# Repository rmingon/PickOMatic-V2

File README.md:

# PickOMatic V2

> **Place faster. Place smarter. The open-source motion controller that turns your pick-and-place ambitions into production reality.**

<p align="center">

</p>

---

**PickOMatic V2** is a professional-grade, all-in-one motion control board designed from the ground up for desktop pick-and-place machines. It is the second generation of the [PickOMatic](https://github.com/rmingon/PickOMatic) motion controller, rebuilt around a modern 32-bit **RISC-V** microcontroller with native **Ethernet** and **USB-C** connectivity.

One board drives the entire machine: gantry, picker heads, nozzles, vacuum, lighting and feedback, with no shields, no breakout spaghetti and no compromises.

## Highlights

- **RISC-V power** : WCH **CH32V317VCT6** (QingKe 32-bit RISC-V core, LQFP-100), a massive leap over the 8-bit ATmega2560 of V1
- **7 stepper channels** : on-board **DRV8825** drivers for the XY gantry, Z axis and auxiliary picker-head axes, each with per-channel microstepping selection (M0/M1/M2 solder jumpers) and current trim
- **Ethernet on board** : integrated PHY with RJ45 magjack (HR911105A) for fast, reliable G-code streaming over the network
- **USB-C** : modern connectivity for setup, control and firmware workflows
- **Vacuum and pneumatics** : dedicated relay outputs (NC-COM-NO) for the vacuum pump and pneumatic accessories
- **3 servo outputs** : independent nozzle height / rotation control per picker head
- **5 endstop inputs** : dedicated limit-switch inputs for X, Y and Z homing (dual X and dual Y supported)
- **Inspection lighting** : dedicated LED control output for camera lighting
- **Operator feedback** : on-board buzzer and status LEDs
- **Expansion ready** : I²C bus, custom headers, FTDI UART header, SWD debug port and BOOT jumpers
- **Clean power architecture** : single 12 V input with on-board buck converters (TPS562200) and LDO rails for logic

## What's new in V2

| | PickOMatic V1 | **PickOMatic V2** |
|---|---|---|
| Microcontroller | ATmega2560 @ 16 MHz (8-bit AVR) | **CH32V317VCT6 (32-bit RISC-V)** |
| Host link | USB-UART (CH340C) | **Native USB-C + Ethernet (RJ45)** |
| Stepper channels | 8 | 7 x DRV8825 with per-axis microstep jumpers |
| Debug / programming | AVR-ISP | **SWD + FTDI UART + BOOT jumpers** |
| Networking | None | **On-board Ethernet PHY + magjack** |

## Board overview

| PCB layout | Schematic |
|:---:|:---:|
|  |  |

## Specifications

| Subsystem | Detail |
|---|---|
| MCU | WCH CH32V317VCT6, 32-bit RISC-V, LQFP-100, external crystal |
| Motion | 7 x DRV8825 stepper drivers (STEP/DIR), microstepping via M0/M1/M2 solder jumpers, current trim potentiometers |
| Axes | Dual-Y and dual-X gantry support, Z axis, auxiliary picker-head channels |
| Endstops | 5 inputs (Z, X-X, Y-Y) on a dedicated header |
| Servos | 3 PWM outputs for nozzle actuation |
| Pneumatics | Relay outputs with NC-COM-NO terminals for vacuum pump control |
| Lighting | Dedicated LED_CTL output for inspection lighting |
| Connectivity | USB-C, 10M Ethernet (RJ45 HR911105A), I²C expansion, FTDI UART |
| Debug | SWD (SWCLK/SWDIO), BOOT0/BOOT1 jumpers, reset button |
| Feedback | Buzzer, status LEDs |
| Power input | 12 V DC via screw terminal |
| Power rails | 12 V motor rail, 5 V and 3.3 V logic rails (TPS562200 buck converters + LDOs) |
| Form factor | 4-corner mounting holes, screw-terminal I/O on board edges |

## Repository structure

```
PickOMatic-V2/
├── hardware/               # KiCad project (schematic + PCB)
│   ├── hardware.kicad_pro
│   ├── hardware.kicad_sch
│   └── hardware.kicad_pcb
├── 3d.png                  # 3D render of the assembled board
├── pcb.png                 # PCB layout view
├── schematic.png           # Full schematic
├── LICENSE                 # CERN-OHL-S v2
└── README.md
```

## Getting started

1. **Clone** the repository
   ```bash
   git clone https://github.com/rmingon/PickOMatic-V2.git
   ```
2. **Open** `hardware/hardware.kicad_pro` in [KiCad](https://www.kicad.org/) (version 8 or later recommended)
3. **Review** the schematic and PCB, then export Gerbers and the BOM for your fab house
4. **Assemble**, set the DRV8825 current limits, configure microstepping with the solder jumpers, and connect your motors, endstops, servos and vacuum pump
5. **Flash** your firmware via SWD or the FTDI/BOOT bootloader path, and start placing parts

## Related projects

- [PickOMatic (V1)](https://github.com/rmingon/PickOMatic) : the original ATmega2560-based motion controller this board evolved from

## Contributing

Issues and pull requests are welcome. If you build a machine around PickOMatic V2, share it: photos, firmware ports and feeder designs all help the project grow.

## License

This project is open-source hardware, released under the **CERN Open Hardware Licence Version 2, Strongly Reciprocal (CERN-OHL-S-2.0)**.

You may use, study, modify, manufacture and distribute this design, provided that any modified versions are released under the same licence and that source is made available. See [LICENSE](LICENSE) for the full text.

Copyright © 2026 [rmingon](https://github.com/rmingon)

---

<p align="center"><i>PickOMatic V2, because your components deserve to be placed with confidence.</i></p>

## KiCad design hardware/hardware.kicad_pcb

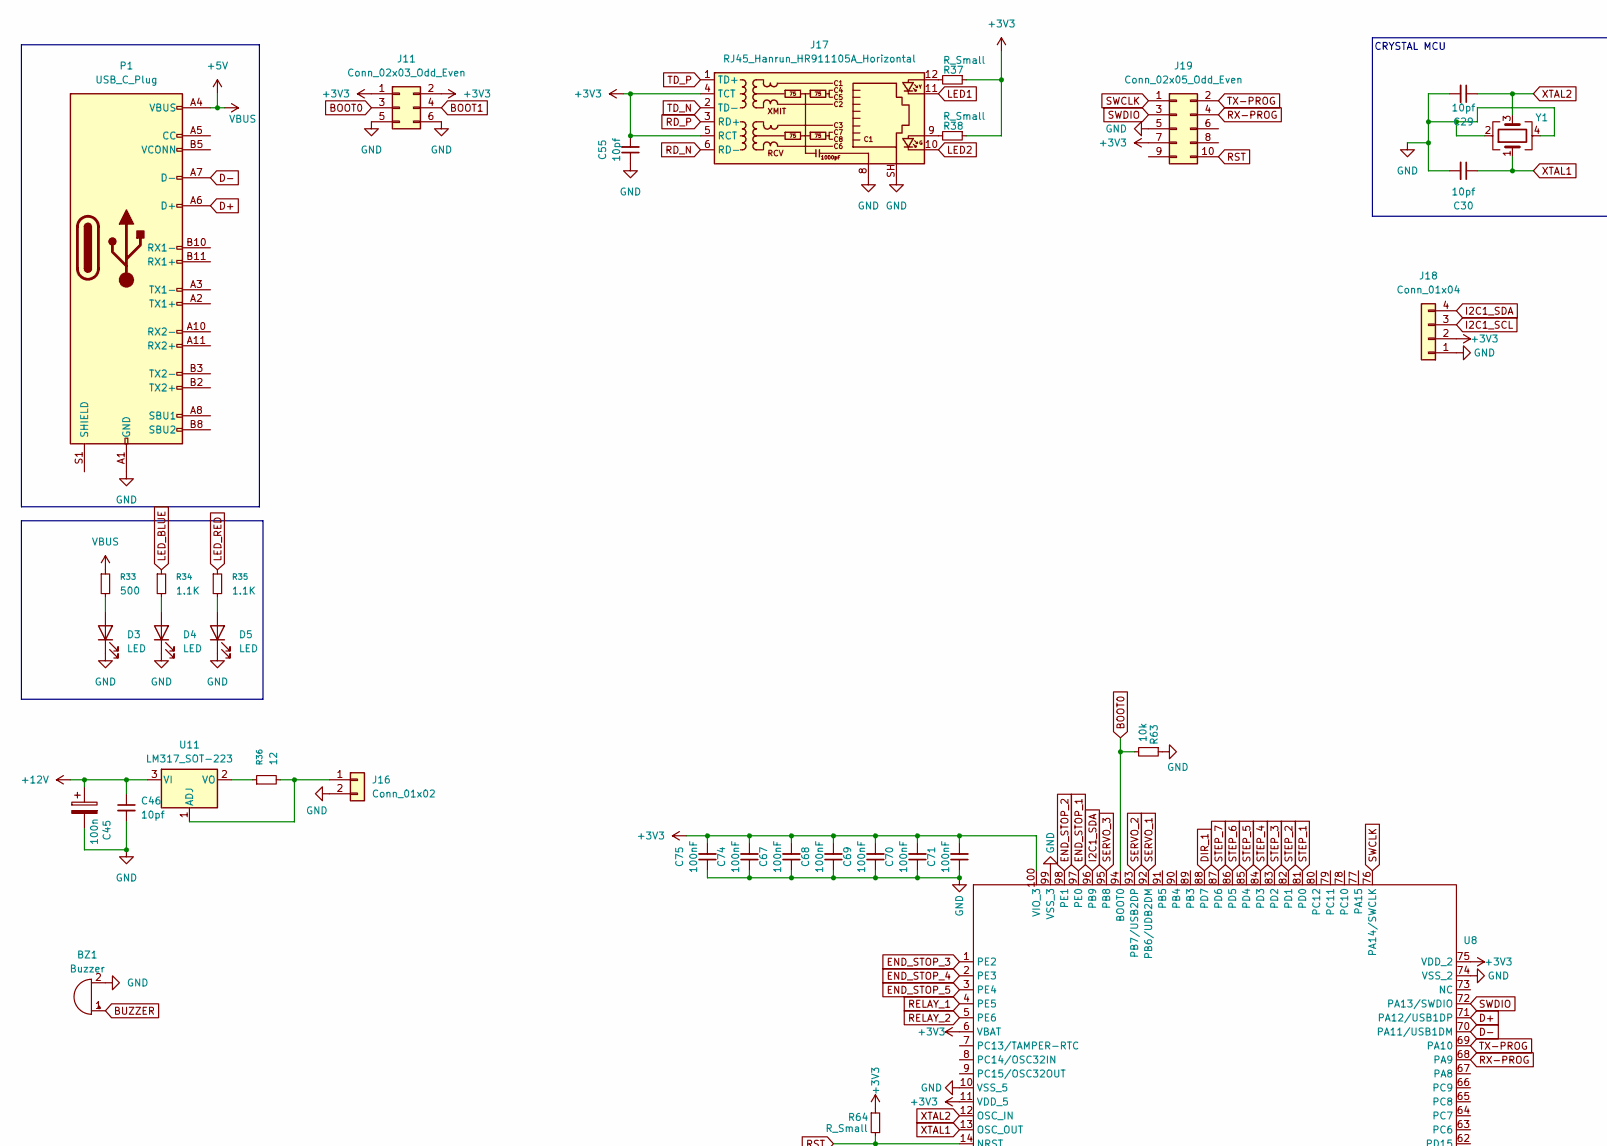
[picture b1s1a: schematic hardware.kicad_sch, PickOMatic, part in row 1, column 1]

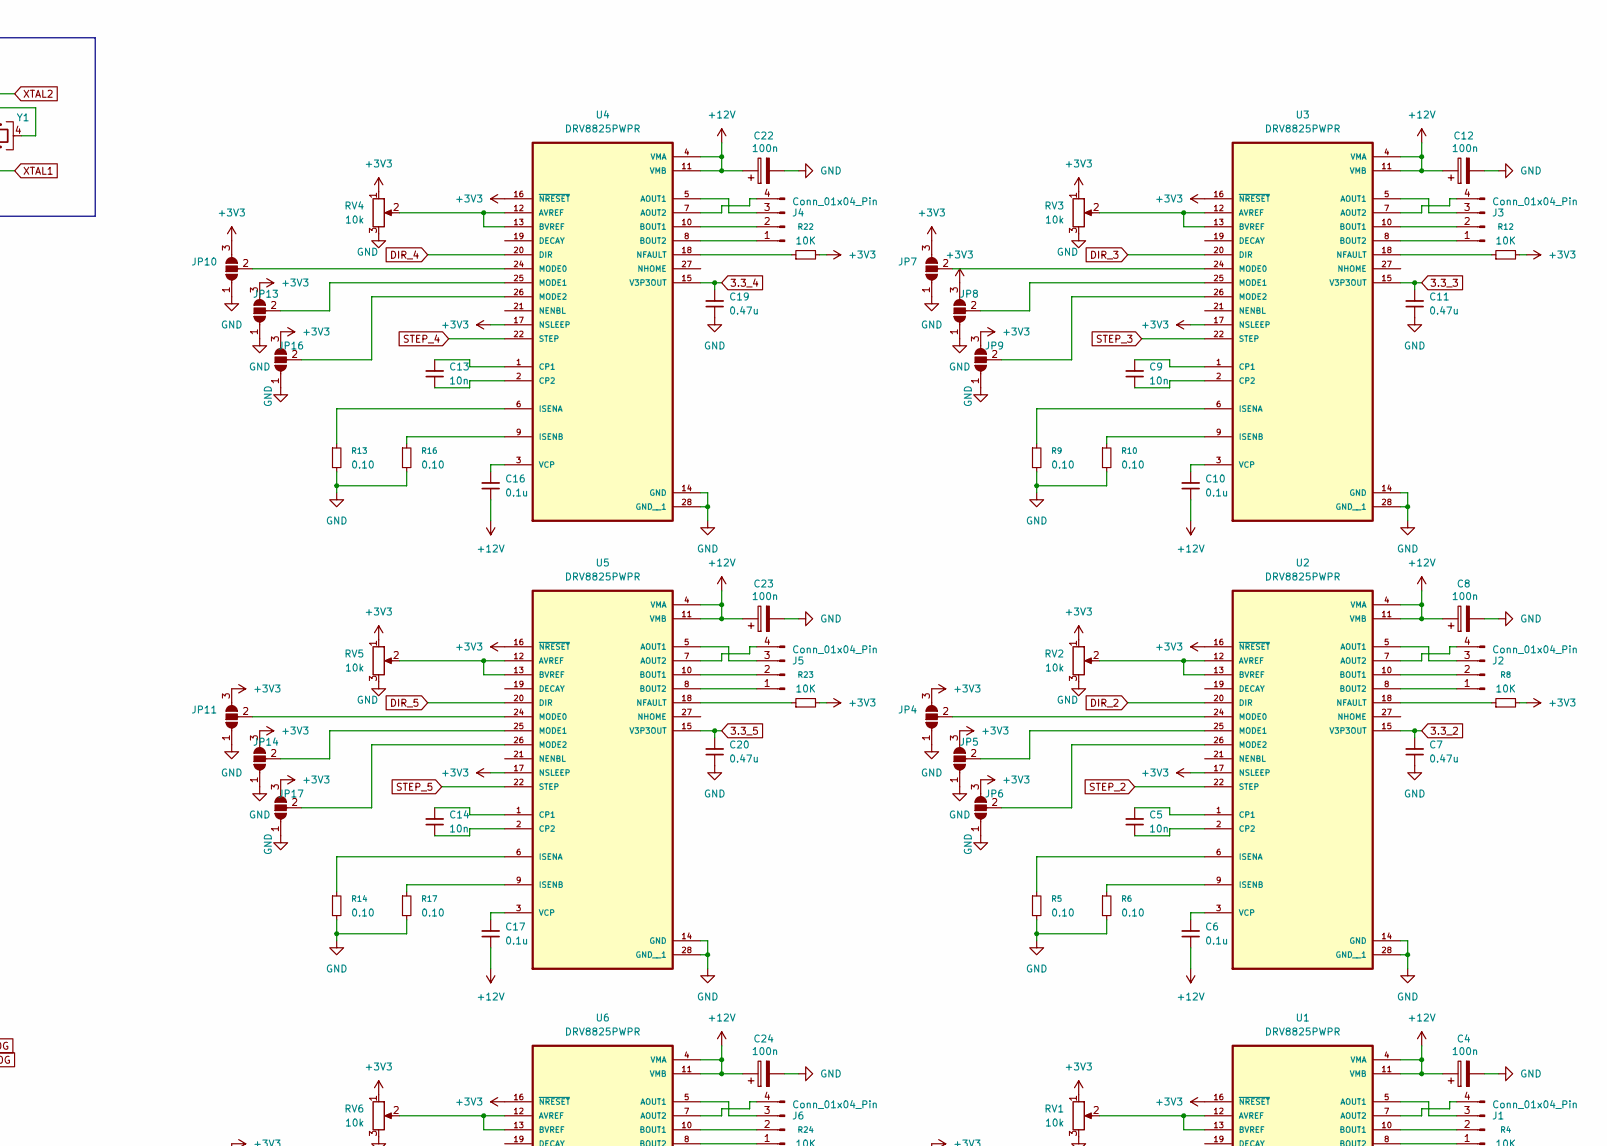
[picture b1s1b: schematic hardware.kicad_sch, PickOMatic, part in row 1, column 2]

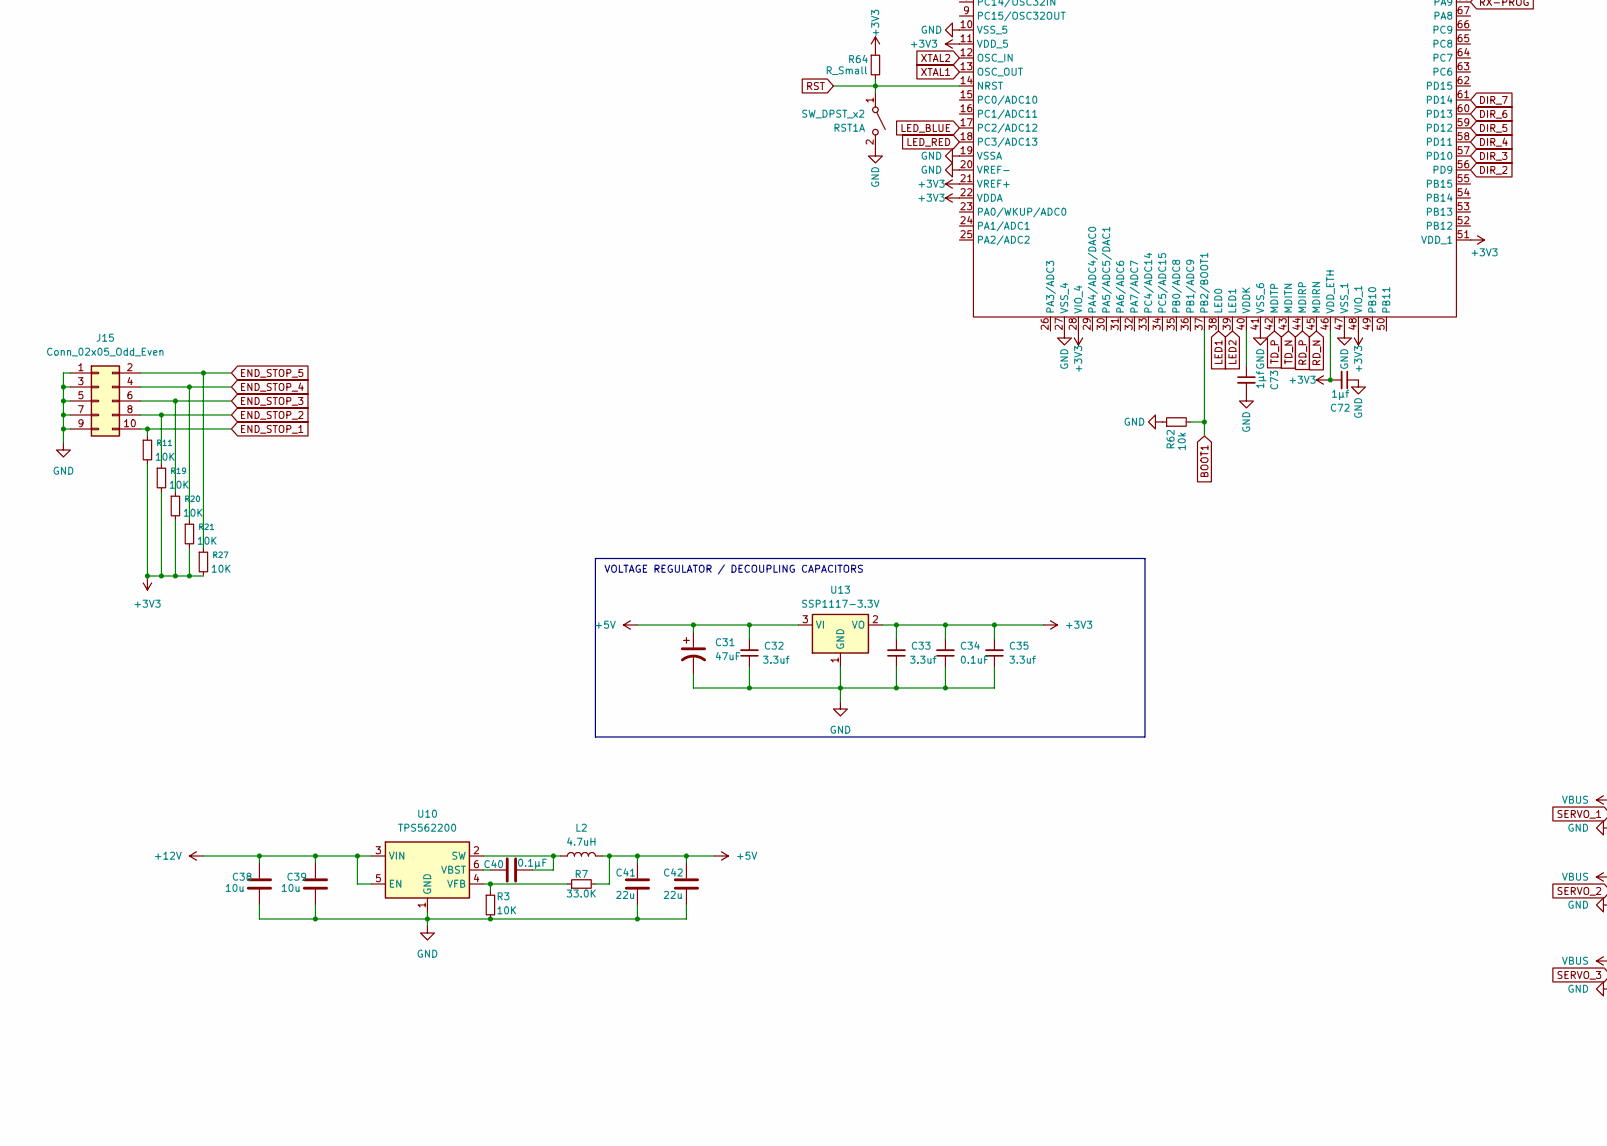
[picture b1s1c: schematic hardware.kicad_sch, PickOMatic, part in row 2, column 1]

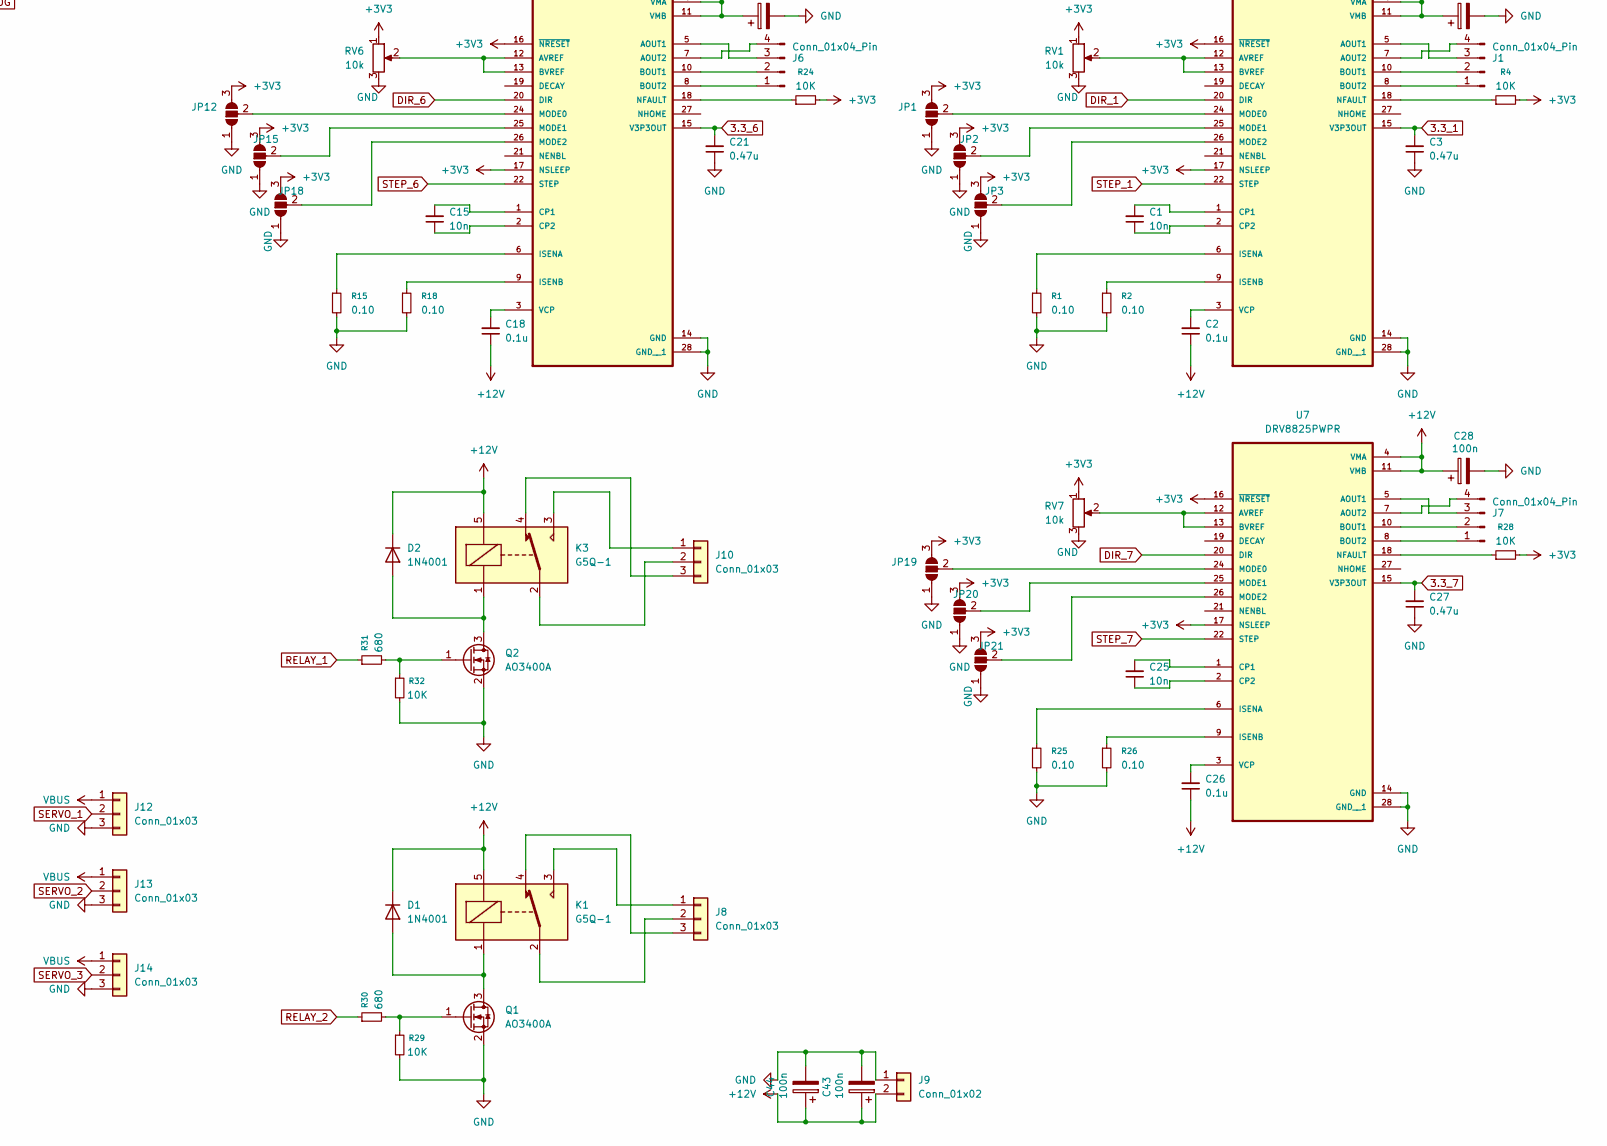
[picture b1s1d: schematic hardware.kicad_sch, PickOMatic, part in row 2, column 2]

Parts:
BZ1: Buzzer; Buzzer_TDK_PS1240P02BT_D12.2mm_H6.5mm
C1, C5, C9, C13, C14, C15, C25: 10n; C_0603_1608Metric
C2, C6, C10, C16, C17, C18, C26: 0.1u; C_0603_1608Metric
C3, C7, C11, C19, C20, C21, C27: 0.47u; C_0603_1608Metric
C4, C8, C12, C22, C23, C24, C28, C43, C44, C45: 100n; CP_Elec_6.3x5.7
C29, C30, C46, C55: 10pf; C_0603_1608Metric; LCSC C106245
C31: 47uF; CP_Elec_6.3x9.9; LCSC C3032930
C32, C33, C35: 3.3uf; C_0603_1608Metric; LCSC C51412
C34: 0.1uF; C_0603_1608Metric; LCSC C14663
C38, C39: 10u; C_0603_1608Metric; LCSC C1691
C40: 0.1µF; C_0603_1608Metric; LCSC C6119867
C41, C42: 22u; C_0603_1608Metric; LCSC C6119867
C67, C68, C69, C70, C71, C74, C75: 100nF; C_0603_1608Metric; LCSC C106245
C72, C73: 1µf; C_0603_1608Metric; LCSC C106245
D1, D2: 1N4001; D_DO-41_SOD81_P10.16mm_Horizontal
D3, D4, D5: LED; LED_0603_1608Metric
J1, J2, J3, J4, J5, J6, J7: Conn_01x04_Pin; TerminalBlock_Phoenix_MPT-0,5-4-2.54_1x04_P2.54mm_Horizontal
J8, J10: Conn_01x03; TerminalBlock_TE_282834-3_1x03_P2.54mm_Horizontal
J9: Conn_01x02; TerminalBlock_Phoenix_PT-1,5-2-3.5-H_1x02_P3.50mm_Horizontal
J11: Conn_02x03_Odd_Even; PinHeader_2x03_P2.54mm_Vertical
J12, J13, J14: Conn_01x03; PinHeader_1x03_P2.54mm_Vertical
J15, J19: Conn_02x05_Odd_Even; PinHeader_2x05_P2.54mm_Vertical
J16: Conn_01x02; Molex_KK-254_AE-6410-02A_1x02_P2.54mm_Vertical
J17: RJ45_Hanrun_HR911105A_Horizontal
J18: Conn_01x04; PinHeader_1x04_P2.54mm_Vertical
JP1, JP2, JP3, JP4, JP5, JP6, JP7, JP8, JP9, JP10, JP11, JP12, JP13, JP14, JP15, JP16, JP17, JP18, JP19, JP20, JP21: SolderJumper_3_Open; SolderJumper-3_P1.3mm_Open_RoundedPad1.0x1.5mm
K1, K3: G5Q-1; Relay_SPDT_Omron-G5Q-1
L2: 4.7uH; L_Chilisin_BMRA00050520; LCSC C3002619
P1: USB_C_Plug; USB_C_Receptacle_GCT_USB4105-xx-A_16P_TopMnt_Horizontal
Q1, Q2: AO3400A; SOT-23
R1, R2, R5, R6, R9, R10, R13, R14, R15, R16, R17, R18, R25, R26: 0.10; R_0603_1608Metric
R3: 10K; R_0603_1608Metric; LCSC C25804
R4, R8, R11, R12, R19, R20, R21, R22, R23, R24, R27, R28, R29, R32: 10K; R_0603_1608Metric
R7: 33.0K; R_0603_1608Metric; LCSC C4216
R30, R31: 680; R_0603_1608Metric
R33: 500; R_0603_1608Metric
R34, R35: 1.1K; R_0603_1608Metric
R36: 12; R_1206_3216Metric
R37, R38, R64: R_Small; R_0603_1608Metric
R62, R63: 10k; R_0603_1608Metric
RST1: SW_DPST_x2; SW_Push_1P1T_NO_CK_KMR2
RV1, RV2, RV3, RV4, RV5, RV6, RV7: 10k; Potentiometer_Bourns_3269W_Vertical
U1, U2, U3, U4, U5, U6, U7: DRV8825PWPR; IC_TPS61196PWPRQ1
U8: LQFP-100_14x14mm_P0.5mm
U10: TPS562200; SOT-23-6; LCSC C49757
U11: LM317_SOT-223; SOT-223-3_TabPin2
U13: SSP1117-3.3V; SOT-223-3_TabPin2; LCSC C277892
Y1: Crystal_GND24; Crystal_SMD_3225-4Pin_3.2x2.5mm_HandSoldering

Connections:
3.3_1: C3.2, U1.15 (V3P3OUT)
3.3_2: C7.2, U2.15 (V3P3OUT)
3.3_3: C11.2, U3.15 (V3P3OUT)
3.3_4: C19.2, U4.15 (V3P3OUT)
3.3_5: C20.2, U5.15 (V3P3OUT)
3.3_6: C21.2, U6.15 (V3P3OUT)
3.3_7: C27.2, U7.15 (V3P3OUT)
+3V3: C33.2, C34.2, C35.2, C55.2, C67.2, C68.2, C69.2, C70.2, C71.2, C72.2, C74.2, C75.2, J11.1, J11.2, J17.4 (TCT), J17.5 (RCT), J18.2, J19.7, JP1.3 (B), JP2.3 (B), JP3.3 (B), JP4.3 (B), JP5.3 (B), JP6.3 (B), JP7.3 (B), JP8.3 (B), JP9.3 (B), JP10.3 (B), JP11.3 (B), JP12.3 (B), JP13.3 (B), JP14.3 (B), JP15.3 (B), JP16.3 (B), JP17.3 (B), JP18.3 (B), JP19.3 (B), JP20.3 (B), JP21.3 (B), R4.2, R8.2, R11.2, R12.2, R19.2, R20.2, R21.2, R22.2, R23.2, R24.2, R27.2, R28.2, R37.1, R38.1, R64.1, RV1.1, RV2.1, RV3.1, RV4.1, RV5.1, RV6.1, RV7.1, U1.16 (~NRESET), U1.17 (NSLEEP), U2.16 (~NRESET), U2.17 (NSLEEP), U3.16 (~NRESET), U3.17 (NSLEEP), U4.16 (~NRESET), U4.17 (NSLEEP), U5.16 (~NRESET), U5.17 (NSLEEP), U6.16 (~NRESET), U6.17 (NSLEEP), U7.16 (~NRESET), U7.17 (NSLEEP), U8.6 (VBAT), U8.11 (VDD_5), U8.21 (VREF+), U8.22 (VDDA), U8.28 (VIO_4), U8.46 (VDD_ETH), U8.48 (VIO_1), U8.51 (VDD_1), U8.75 (VDD_2), U8.100 (VIO_3), U13.2 (VO)
+5V: C31.1, C32.2, C41.1, C42.1, J12.1, J13.1, J14.1, L2.2, P1.A4 (VBUS), P1.A9 (VBUS), P1.B4 (VBUS), P1.B9 (VBUS), R7.2, R33.1, U13.3 (VI)
+12V: C2.1, C4.1, C6.1, C8.1, C10.1, C12.1, C16.1, C17.1, C18.1, C22.1, C23.1, C24.1, C26.1, C28.1, C38.1, C39.1, C43.1, C44.1, C45.1, C46.1, D1.1 (K), D2.1 (K), J9.2, K1.5, K3.5, U1.4 (VMA), U1.11 (VMB), U2.4 (VMA), U2.11 (VMB), U3.4 (VMA), U3.11 (VMB), U4.4 (VMA), U4.11 (VMB), U5.4 (VMA), U5.11 (VMB), U6.4 (VMA), U6.11 (VMB), U7.4 (VMA), U7.11 (VMB), U10.3 (VIN), U10.5 (EN), U11.3 (VI)
BOOT0: J11.3, R63.2, U8.94 (BOOT0)
BOOT1: J11.4, R62.2, U8.37 (PB2/BOOT1)
BUZZER: BZ1.1 (+)
D+: P1.A6 (D+), U8.71 (PA12/USB1DP)
D-: P1.A7 (D-), U8.70 (PA11/USB1DM)
DIR_1: U1.20 (DIR), U8.88 (PD7)
DIR_2: U2.20 (DIR), U8.56 (PD9)
DIR_3: U3.20 (DIR), U8.57 (PD10)
DIR_4: U4.20 (DIR), U8.58 (PD11)
DIR_5: U5.20 (DIR), U8.59 (PD12)
DIR_6: U6.20 (DIR), U8.60 (PD13)
DIR_7: U7.20 (DIR), U8.61 (PD14)
END_STOP_1: J15.10, R11.1, U8.97 (PE0)
END_STOP_2: J15.8, R19.1, U8.98 (PE1)
END_STOP_3: J15.6, R20.1, U8.1 (PE2)
END_STOP_4: J15.4, R21.1, U8.2 (PE3)
END_STOP_5: J15.2, R27.1, U8.3 (PE4)
GND: BZ1.2 (-), C3.1, C4.2, C7.1, C8.2, C11.1, C12.2, C19.1, C20.1, C21.1, C22.2, C23.2, C24.2, C27.1, C28.2, C29.2, C30.2, C31.2, C32.1, C33.1, C34.1, C35.1, C38.2, C39.2, C41.2, C42.2, C43.2, C44.2, C45.2, C46.2, C55.1, C67.1, C68.1, C69.1, C70.1, C71.1, C72.1, C73.2, C74.1, C75.1, D3.1 (K), D4.1 (K), D5.1 (K), J9.1, J11.5, J11.6, J12.3, J13.3, J14.3, J15.1, J15.3, J15.5, J15.7, J15.9, J16.2, J17.8, J17.SH, J18.1, J19.5, JP1.1 (A), JP2.1 (A), JP3.1 (A), JP4.1 (A), JP5.1 (A), JP6.1 (A), JP7.1 (A), JP8.1 (A), JP9.1 (A), JP10.1 (A), JP11.1 (A), JP12.1 (A), JP13.1 (A), JP14.1 (A), JP15.1 (A), JP16.1 (A), JP17.1 (A), JP18.1 (A), JP19.1 (A), JP20.1 (A), JP21.1 (A), P1.A1 (GND), P1.A12 (GND), P1.B1 (GND), P1.B12 (GND), Q1.2 (S), Q2.2 (S), R1.2, R2.2, R3.2, R5.2, R6.2, R9.2, R10.2, R13.2, R14.2, R15.2, R16.2, R17.2, R18.2, R25.2, R26.2, R29.2, R32.2, R62.1, R63.1, RST1.2 (B), RV1.3, RV2.3, RV3.3, RV4.3, RV5.3, RV6.3, RV7.3, U1.14 (GND), U1.28 (GND__1), U2.14 (GND), U2.28 (GND__1), U3.14 (GND), U3.28 (GND__1), U4.14 (GND), U4.28 (GND__1), U5.14 (GND), U5.28 (GND__1), U6.14 (GND), U6.28 (GND__1), U7.14 (GND), U7.28 (GND__1), U8.10 (VSS_5), U8.19 (VSSA), U8.20 (VREF-), U8.27 (VSS_4), U8.41 (VSS_6), U8.47 (VSS_1), U8.74 (VSS_2), U8.99 (VSS_3), U10.1 (GND), U13.1 (GND), Y1.2, Y1.4
I2C1_SCL: J18.3
I2C1_SDA: J18.4, U8.96 (PB9)
LED1: J17.11, U8.38 (LED0)
LED2: J17.10, U8.39 (LED1)
LED_BLUE: R34.1, U8.17 (PC2/ADC12)
LED_RED: R35.1, U8.18 (PC3/ADC13)
unnamed: D1.2 (A), K1.1, Q1.3 (D)
unnamed: D2.2 (A), K3.1, Q2.3 (D)
unnamed: D3.2 (A), R33.2
unnamed: D4.2 (A), R34.2
unnamed: D5.2 (A), R35.2
unnamed: J1.1, U1.8 (BOUT2)
unnamed: J1.2, U1.10 (BOUT1)
unnamed: J1.3, U1.5 (AOUT1)
unnamed: J1.4, U1.7 (AOUT2)
unnamed: J2.1, U2.8 (BOUT2)
unnamed: J2.2, U2.10 (BOUT1)
unnamed: J2.3, U2.5 (AOUT1)
unnamed: J2.4, U2.7 (AOUT2)
unnamed: J3.1, U3.8 (BOUT2)
unnamed: J3.2, U3.10 (BOUT1)
unnamed: J3.3, U3.5 (AOUT1)
unnamed: J3.4, U3.7 (AOUT2)
unnamed: J4.1, U4.8 (BOUT2)
unnamed: J4.2, U4.10 (BOUT1)
unnamed: J4.3, U4.5 (AOUT1)
unnamed: J4.4, U4.7 (AOUT2)
unnamed: J5.1, U5.8 (BOUT2)
unnamed: J5.2, U5.10 (BOUT1)
unnamed: J5.3, U5.5 (AOUT1)
unnamed: J5.4, U5.7 (AOUT2)
unnamed: J6.1, U6.8 (BOUT2)
unnamed: J6.2, U6.10 (BOUT1)
unnamed: J6.3, U6.5 (AOUT1)
unnamed: J6.4, U6.7 (AOUT2)
unnamed: J7.1, U7.8 (BOUT2)
unnamed: J7.2, U7.10 (BOUT1)
unnamed: J7.3, U7.5 (AOUT1)
unnamed: J7.4, U7.7 (AOUT2)
unnamed: J8.1, K1.3
unnamed: J8.2, K1.2
unnamed: J8.3, K1.4
unnamed: J10.1, K3.3
unnamed: J10.2, K3.2
unnamed: J10.3, K3.4
unnamed: J16.1, R36.2, U11.1 (ADJ)
unnamed: J17.9, R38.2
unnamed: J17.12, R37.2
unnamed: JP1.2 (C), U1.24 (MODE0)
unnamed: JP2.2 (C), U1.25 (MODE1)
unnamed: JP3.2 (C), U1.26 (MODE2)
unnamed: JP4.2 (C), U2.24 (MODE0)
unnamed: JP5.2 (C), U2.25 (MODE1)
unnamed: JP6.2 (C), U2.26 (MODE2)
unnamed: JP7.2 (C), U3.24 (MODE0)
unnamed: JP8.2 (C), U3.25 (MODE1)
unnamed: JP9.2 (C), U3.26 (MODE2)
unnamed: JP10.2 (C), U4.24 (MODE0)
unnamed: JP11.2 (C), U5.24 (MODE0)
unnamed: JP12.2 (C), U6.24 (MODE0)
unnamed: JP13.2 (C), U4.25 (MODE1)
unnamed: JP14.2 (C), U5.25 (MODE1)
unnamed: JP15.2 (C), U6.25 (MODE1)
unnamed: JP16.2 (C), U4.26 (MODE2)
unnamed: JP17.2 (C), U5.26 (MODE2)
unnamed: JP18.2 (C), U6.26 (MODE2)
unnamed: JP19.2 (C), U7.24 (MODE0)
unnamed: JP20.2 (C), U7.25 (MODE1)
unnamed: JP21.2 (C), U7.26 (MODE2)
unnamed: Q1.1 (G), R29.1, R30.2
unnamed: Q2.1 (G), R31.2, R32.1
unnamed: RV1.2, U1.12 (AVREF), U1.13 (BVREF)
unnamed: C1.2, U1.1 (CP1)
unnamed: C1.1, U1.2 (CP2)
unnamed: R1.1, U1.6 (ISENA)
unnamed: R2.1, U1.9 (ISENB)
unnamed: R4.1, U1.18 (NFAULT)
unnamed: C2.2, U1.3 (VCP)
unnamed: RV2.2, U2.12 (AVREF), U2.13 (BVREF)
unnamed: C5.2, U2.1 (CP1)
unnamed: C5.1, U2.2 (CP2)
unnamed: R5.1, U2.6 (ISENA)
unnamed: R6.1, U2.9 (ISENB)
unnamed: R8.1, U2.18 (NFAULT)
unnamed: C6.2, U2.3 (VCP)
unnamed: RV3.2, U3.12 (AVREF), U3.13 (BVREF)
unnamed: C9.2, U3.1 (CP1)
unnamed: C9.1, U3.2 (CP2)
unnamed: R9.1, U3.6 (ISENA)
unnamed: R10.1, U3.9 (ISENB)
unnamed: R12.1, U3.18 (NFAULT)
unnamed: C10.2, U3.3 (VCP)
unnamed: RV4.2, U4.12 (AVREF), U4.13 (BVREF)
unnamed: C13.2, U4.1 (CP1)
unnamed: C13.1, U4.2 (CP2)
unnamed: R13.1, U4.6 (ISENA)
unnamed: R16.1, U4.9 (ISENB)
unnamed: R22.1, U4.18 (NFAULT)
unnamed: C16.2, U4.3 (VCP)
unnamed: RV5.2, U5.12 (AVREF), U5.13 (BVREF)
unnamed: C14.2, U5.1 (CP1)
unnamed: C14.1, U5.2 (CP2)
unnamed: R14.1, U5.6 (ISENA)
unnamed: R17.1, U5.9 (ISENB)
unnamed: R23.1, U5.18 (NFAULT)
unnamed: C17.2, U5.3 (VCP)
unnamed: RV6.2, U6.12 (AVREF), U6.13 (BVREF)
unnamed: C15.2, U6.1 (CP1)
unnamed: C15.1, U6.2 (CP2)
unnamed: R15.1, U6.6 (ISENA)
unnamed: R18.1, U6.9 (ISENB)
unnamed: R24.1, U6.18 (NFAULT)
unnamed: C18.2, U6.3 (VCP)
unnamed: RV7.2, U7.12 (AVREF), U7.13 (BVREF)
unnamed: C25.2, U7.1 (CP1)
unnamed: C25.1, U7.2 (CP2)
unnamed: R25.1, U7.6 (ISENA)
unnamed: R26.1, U7.9 (ISENB)
unnamed: R28.1, U7.18 (NFAULT)
unnamed: C26.2, U7.3 (VCP)
unnamed: C73.1, U8.40 (VDDK)
unnamed: C40.2, L2.1, U10.2 (SW)
unnamed: C40.1, U10.6 (VBST)
unnamed: R3.1, R7.1, U10.4 (VFB)
unnamed: R36.1, U11.2 (VO)
RD_N: J17.6 (RD-), U8.45 (MDIRN)
RD_P: J17.3 (RD+), U8.44 (MDIRP)
RELAY_1: R31.1, U8.4 (PE5)
RELAY_2: R30.1, U8.5 (PE6)
RST: J19.10, R64.2, RST1.1 (A), U8.14 (NRST)
RX-PROG: J19.4, U8.68 (PA9)
SERVO_1: J12.2, U8.92 (PB6/UDB2DM)
SERVO_2: J13.2, U8.93 (PB7/USB2DP)
SERVO_3: J14.2, U8.95 (PB8)
STEP_1: U1.22 (STEP), U8.81 (PD0)
STEP_2: U2.22 (STEP), U8.82 (PD1)
STEP_3: U3.22 (STEP), U8.83 (PD2)
STEP_4: U4.22 (STEP), U8.84 (PD3)
STEP_5: U5.22 (STEP), U8.85 (PD4)
STEP_6: U6.22 (STEP), U8.86 (PD5)
STEP_7: U7.22 (STEP), U8.87 (PD6)
SWCLK: J19.1, U8.76 (PA14/SWCLK)
SWDIO: J19.3, U8.72 (PA13/SWDIO)
TD_N: J17.2 (TD-), U8.43 (MDITN)
TD_P: J17.1 (TD+), U8.42 (MDITP)
TX-PROG: J19.2, U8.69 (PA10)
XTAL1: C30.1, U8.13 (OSC_OUT), Y1.1
XTAL2: C29.1, U8.12 (OSC_IN), Y1.3

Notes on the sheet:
CRYSTAL MCU
VOLTAGE REGULATOR / DECOUPLING CAPACITORS

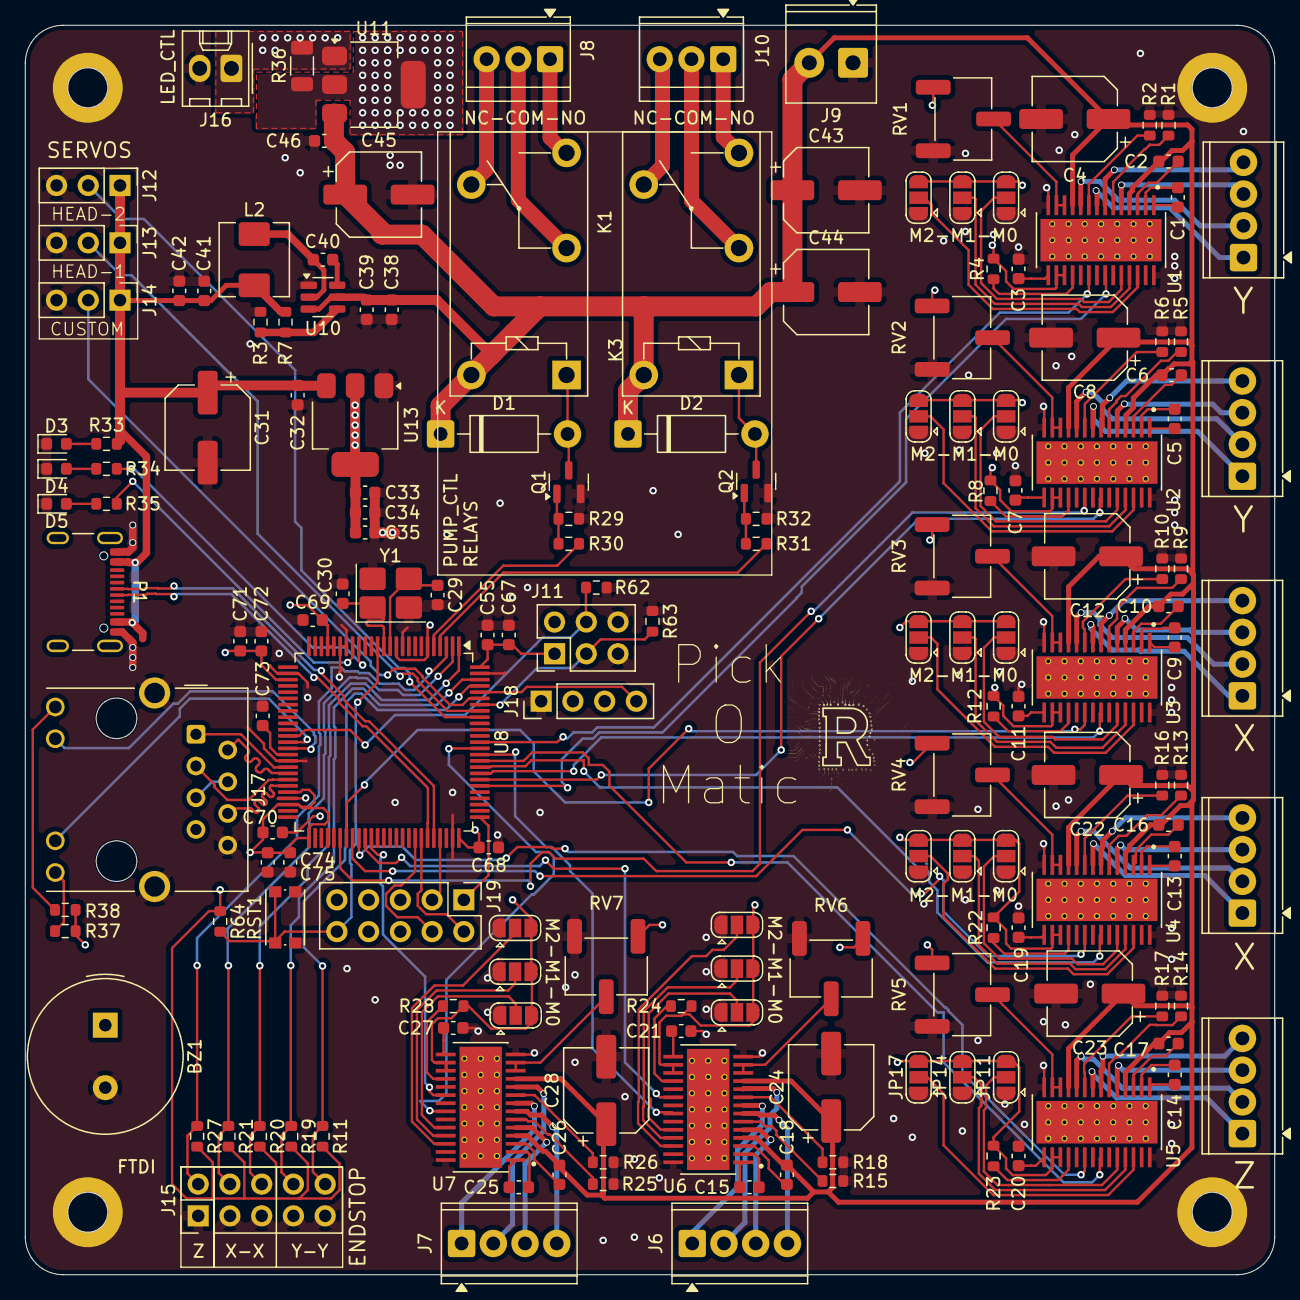
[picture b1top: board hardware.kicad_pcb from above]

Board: 4 copper layers, 100.0 x 100.0 mm, 167 parts (0 on the bottom side), 174 nets.

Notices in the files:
README.md:
License: CERN-OHL-S-2.0
